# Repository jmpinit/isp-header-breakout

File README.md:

# ISP Header Breakout

A little PCB to make it easier/cleaner to attach an in-system programmer to a system.

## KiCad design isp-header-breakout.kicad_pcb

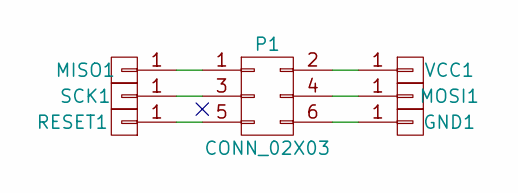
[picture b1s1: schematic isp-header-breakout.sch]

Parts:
GND1: CONN_01X01; Pin_Header_Straight_1x01
MISO1: CONN_01X01; Pin_Header_Straight_1x01
MOSI1: CONN_01X01; Pin_Header_Straight_1x01
P1: CONN_02X03; Pin_Header_Straight_2x03
RESET1: CONN_01X01; Pin_Header_Straight_1x01
SCK1: CONN_01X01; Pin_Header_Straight_1x01
VCC1: CONN_01X01; Pin_Header_Straight_1x01

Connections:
unnamed: GND1.1, P1.6
unnamed: MISO1.1, P1.1
unnamed: MOSI1.1, P1.4
unnamed: P1.2, VCC1.1
unnamed: P1.3, SCK1.1
unnamed: P1.5, RESET1.1

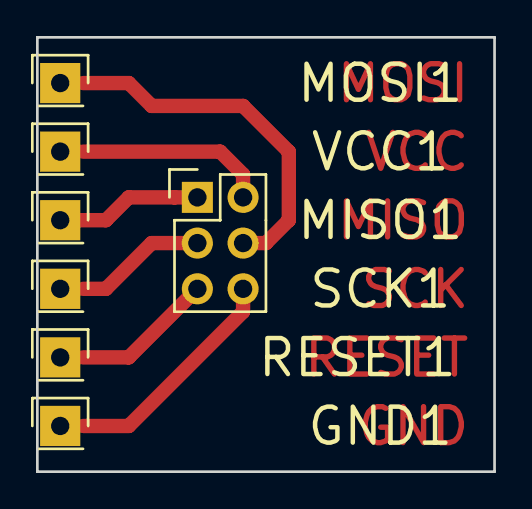
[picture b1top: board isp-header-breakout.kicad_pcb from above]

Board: 2 copper layers, 25.4 x 24.1 mm, 7 parts (0 on the bottom side), 6 nets.

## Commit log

2017-01-01 Add readme
2017-01-01 Create LICENSE
